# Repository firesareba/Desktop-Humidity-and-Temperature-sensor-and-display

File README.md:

# Desktop-Humidity-and-Temperature-sensor-and-display
A Simple Humidity and Temperature sensor and display using the DHT22 TEMP/HUM sensor displaying on the 0.91" OLED used in the Hackpad aswell as the RP2040 used in the same hackpad. Goes on your desk!

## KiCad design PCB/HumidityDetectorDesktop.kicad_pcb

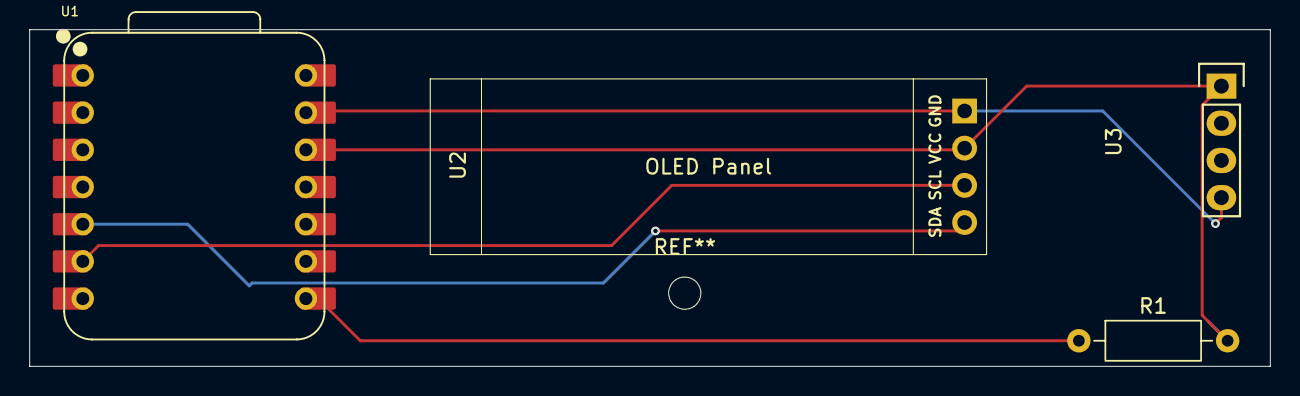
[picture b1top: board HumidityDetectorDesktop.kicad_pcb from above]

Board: 2 copper layers, 84.8 x 23.0 mm, 4 parts (0 on the bottom side), 5 nets.

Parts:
R1: 4.7k; R_Axial_DIN0207_L6.3mm_D2.5mm_P10.16mm_Horizontal
U1: XIAO-RP2040-DIP
U2: SSD1306-0.91-OLED-4pin-128x32
U3: DHT22_Temperature_Humidity

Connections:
unnamed: R1.2, U1.12 (3V3), U2.2 (VCC), U3.1 (VCC)
unnamed: U1.13 (GND), U2.1 (GND), U3.4 (GND)
unnamed: R1.1, U1.8 (GPIO1/RX)
unnamed: U1.5 (GPIO6/SDA), U2.4 (SDA)
unnamed: U1.6 (GPIO7/SCL), U2.3 (SCL)

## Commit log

2025-12-03 Create E
2025-12-03 Fix formatting of Bill of Materials in readme.md
2025-12-05 Rename HumidityDetectorDesktop.csv to w
2025-12-05 Update CSV format for HumidityDetectorDesktop
2025-12-05 Fix formatting in HumidityDetectorDesktop.csv
2025-12-05 Add links and prices to components in CSV
2025-12-05 Add new item for 3D printed case in CSV
2025-12-05 Add PCB Fabrication entry to CSV
2025-12-05 Refine language and improve clarity in readme.md
    Updated wording for clarity and consistency in the readme.
